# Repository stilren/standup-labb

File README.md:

# standup-labb

##Installation##
1. Ladda ner arduino IDE för ditt operativsystem på https://www.arduino.cc/en/Main/Software
2. Om du kör mac kan du behöva installera drivrutiner externt (se instruktioner i mappen /drivers).
3. Ladda ner och zippa upp detta repo på knappen "clone or download" på https://github.com/stilren/standup-labb
4. Flytta allt innehåll i mappen "bibliotek" till \Documents\Arduino\libraries på din dator

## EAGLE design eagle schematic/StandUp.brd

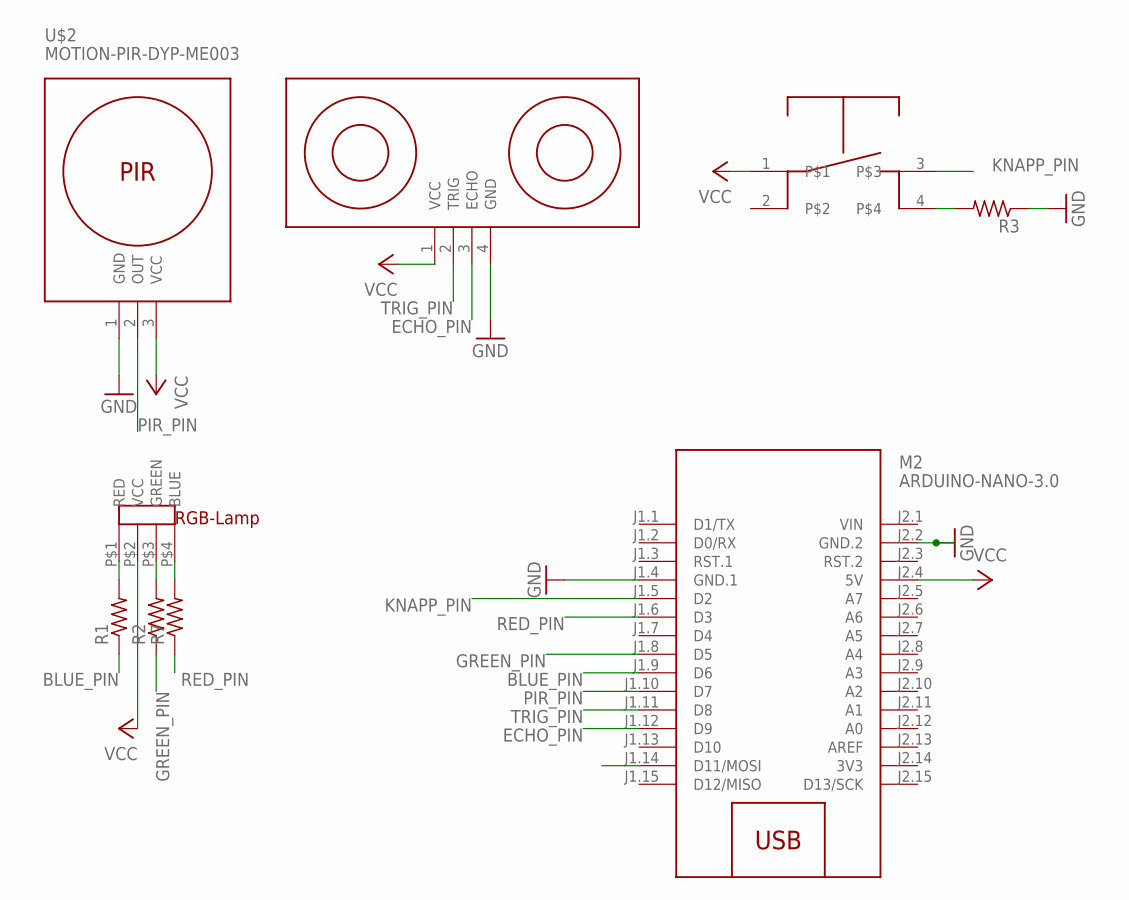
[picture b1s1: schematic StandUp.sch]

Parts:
M2: ARDUINO-NANO-3.0
R1, R2, R3, R7: R-US_0204/7; 0204/7
U$2: MOTION-PIR-DYP-ME003
U$3: ULTRASONIC-HC-SR04#V
U$4: KNAPP-TSA
U$5: RGBLAMP

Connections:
3V3: M2.J2.14 (3V3)
BLUE_PIN: M2.J1.9 (D6), R1.1
ECHO_PIN: M2.J1.12 (D9), U$3.3 (ECHO)
GND: M2.J1.4 (GND.1), M2.J2.2 (GND.2), R3.1, U$2.1 (GND), U$3.4 (GND)
GREEN_PIN: M2.J1.8 (D5), R2.1
KNAPP_PIN: M2.J1.5 (D2), U$4.3
MOSI_SPI: M2.J1.14 (D11/MOSI)
unnamed: R2.2, U$5.P$3 (GREEN)
unnamed: R7.2, U$5.P$4 (BLUE)
unnamed: R1.2, U$5.P$1 (RED)
unnamed: R3.2, U$4.4
PIR_PIN: M2.J1.10 (D7), U$2.2 (OUT)
RED_PIN: M2.J1.6 (D3), R7.1
TRIG_PIN: M2.J1.11 (D8), U$3.2 (TRIG)
VCC: M2.J2.4 (5V), U$2.3 (VCC), U$3.1 (VCC), U$4.1, U$5.P$2 (VCC)
VIN: M2.J2.1 (VIN)

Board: 2 copper layers, 9 parts (1 on the bottom side), 13 nets, no tracks yet.

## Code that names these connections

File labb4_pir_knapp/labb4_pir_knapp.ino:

#include <Chrono.h>
#include <NewPing.h>

const int TRIGGER_PIN = 8;  // Arduino pin tied to trigger pin on the ultrasonic sensor.
const int ECHO_PIN = 9;  // Arduino pin tied to echo pin on the ultrasonic sensor.
const int MAX_DISTANCE = 500; // Maximum distance we want to ping for (in centimeters). Maximum sensor distance is rated at 400-500cm.
const int RED_PIN = 3;
const int GREEN_PIN = 5;
const int BLUE_PIN = 6;
const int BUTTON_PIN = 2;
const int PIR_PIN = 7;

NewPing sonar(TRIGGER_PIN, ECHO_PIN, MAX_DISTANCE); // NewPing setup of pins and maximum distance.
Chrono timeSitting;
Chrono timeAway;

int sittingDistance;
bool isAway = false;

void setup() {
  Serial.begin(9600); // initialize serial communication at 9600 bits per second:
  pinMode(RED_PIN, OUTPUT);
  pinMode(BLUE_PIN, OUTPUT);
  pinMode(GREEN_PIN, OUTPUT);
  pinMode(PIR_PIN, INPUT);
  pinMode(BUTTON_PIN, INPUT);

  sittingDistance = sonar.ping_cm(); //We are assuming the user starts in a sitting state
  timeSitting.start();
  timeAway.start();
}

void loop() {
  /*
   * Read all sensors 
   */
  int distance = sonar.ping_cm();
  bool presence = digitalRead(PIR_PIN);
  bool buttonPress = digitalRead(BUTTON_PIN);

   /*
   * Check is button is pressed 
   * If it is, set new sitting heigt
   */
  if (buttonPress == true) {
    sittingDistance = distance;
    timeSitting.restart();
  }

  /*
   * Set isAway variable
   */
  if (presence == true) {
    timeAway.restart();
  }

  if (timeAway.hasPassed(20000)) {
    isAway = true;
  } 
  else {
    isAway = false;
  }

  /*
   * Set timeSitting variable
   */
  int diff = abs(distance - sittingDistance);
  if(isAway == true){
    timeSitting.stop();
  }
  else if (diff < 10) {
    if(timeSitting.isRunning() == false){
      timeSitting.resume();
    }
  }
  else {
    timeSitting.restart();
  }

  /*
   * Set lamp color
   */
  if(isAway == true){
    setColor(0, 0, 0);
  }
  else if (timeSitting.hasPassed(5000)) {
    setColor(255, 0, 0);
  } 
  else {
    setColor(0, 255, 0);
  }
  Serial.print(diff); Serial.print(" , "); Serial.print(presence); Serial.print(" , ");
  Serial.println(timeSitting.elapsed());
  
  delay(30);
}

void setColor(int red, int green, int blue) {
  digitalWrite(RED_PIN, 255 - red);
  digitalWrite(GREEN_PIN, 255 - green);
  digitalWrite(BLUE_PIN, 255 - blue);
}

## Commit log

2016-10-29 initcommit
2016-10-29 init commit 2
2016-10-30 added last labs and eagle files
2016-10-31 added drivers for mac & win

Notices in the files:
parts and their libraries:
diy-modules: Released under the Creative Commons Attribution 4.0 International License: http://creativecommons.org/licenses/by/4.0
